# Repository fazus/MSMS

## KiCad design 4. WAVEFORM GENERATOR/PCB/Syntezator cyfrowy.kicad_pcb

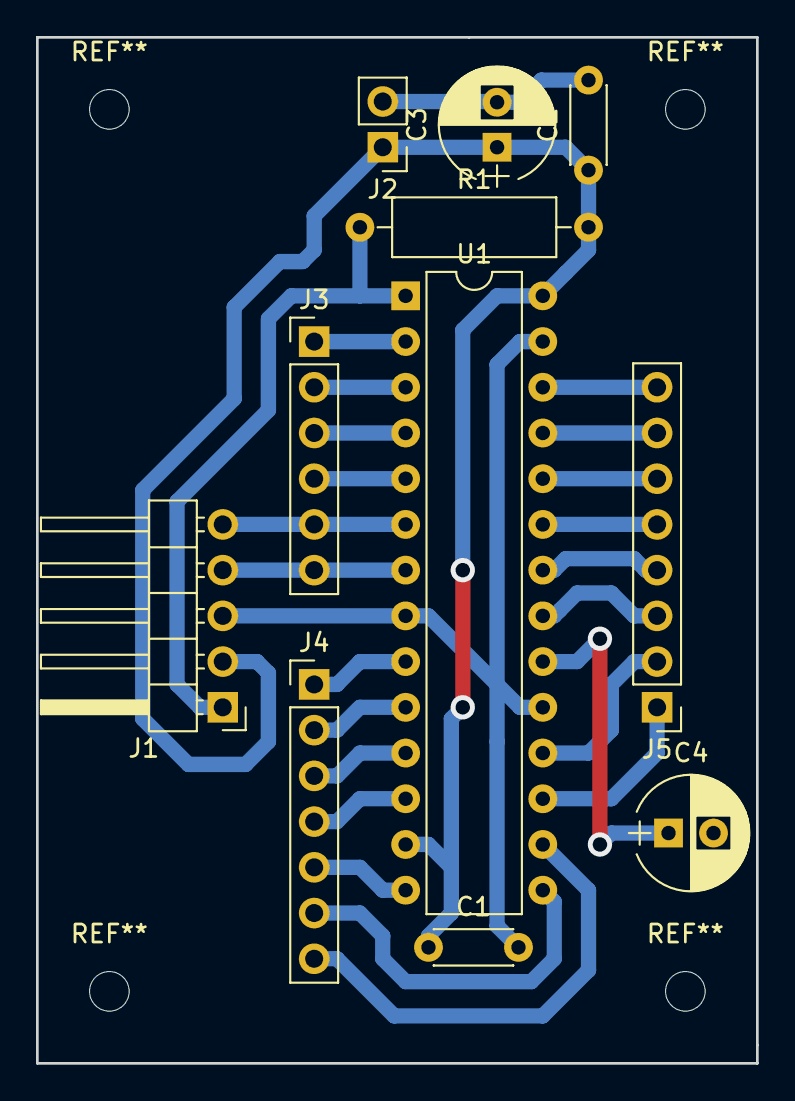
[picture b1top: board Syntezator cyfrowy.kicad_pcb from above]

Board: 2 copper layers, 40.0 x 57.0 mm, 11 parts (0 on the bottom side), 25 nets.

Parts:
C1, C2: C; C_Disc_D4.3mm_W1.9mm_P5.00mm
C3, C4: CP; CP_Radial_D6.3mm_P2.50mm
J1: Conn_01x05; Pin_Header_Angled_1x05_Pitch2.54mm
J2: Conn_01x02; Pin_Header_Straight_1x02_Pitch2.54mm
J3: Conn_01x06; Pin_Header_Straight_1x06_Pitch2.54mm
J4: Conn_01x07; Pin_Header_Straight_1x07_Pitch2.54mm
J5: Conn_01x08; Pin_Header_Straight_1x08_Pitch2.54mm
R1: R; R_Axial_DIN0309_L9.0mm_D3.2mm_P12.70mm_Horizontal
U1: DSPIC33EP256GP502; DIP-28_W7.62mm

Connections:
+3V3: C1.1, C2.1, C3.1, J1.2, J2.1, R1.2, U1.13, U1.28
GND: C1.2, C2.2, C3.2, C4.2, J1.3, J2.2, U1.8, U1.19, U1.27
unnamed: C4.1, U1.20
unnamed: J1.1, R1.1, U1.1
unnamed: J1.4, J3.6, U1.7
unnamed: J1.5, J3.5, U1.6
unnamed: J3.1, U1.2
unnamed: J3.2, U1.3
unnamed: J3.3, U1.4
unnamed: J3.4, U1.5
unnamed: J4.1, U1.9
unnamed: J4.2, U1.10
unnamed: J4.3, U1.11
unnamed: J4.4, U1.12
unnamed: J4.5, U1.14
unnamed: J4.6, U1.15
unnamed: J4.7, U1.16
unnamed: J5.1, U1.17
unnamed: J5.2, U1.18
unnamed: J5.3, U1.21
unnamed: J5.4, U1.22
unnamed: J5.5, U1.23
unnamed: J5.6, U1.24
unnamed: J5.7, U1.25
unnamed: J5.8, U1.26

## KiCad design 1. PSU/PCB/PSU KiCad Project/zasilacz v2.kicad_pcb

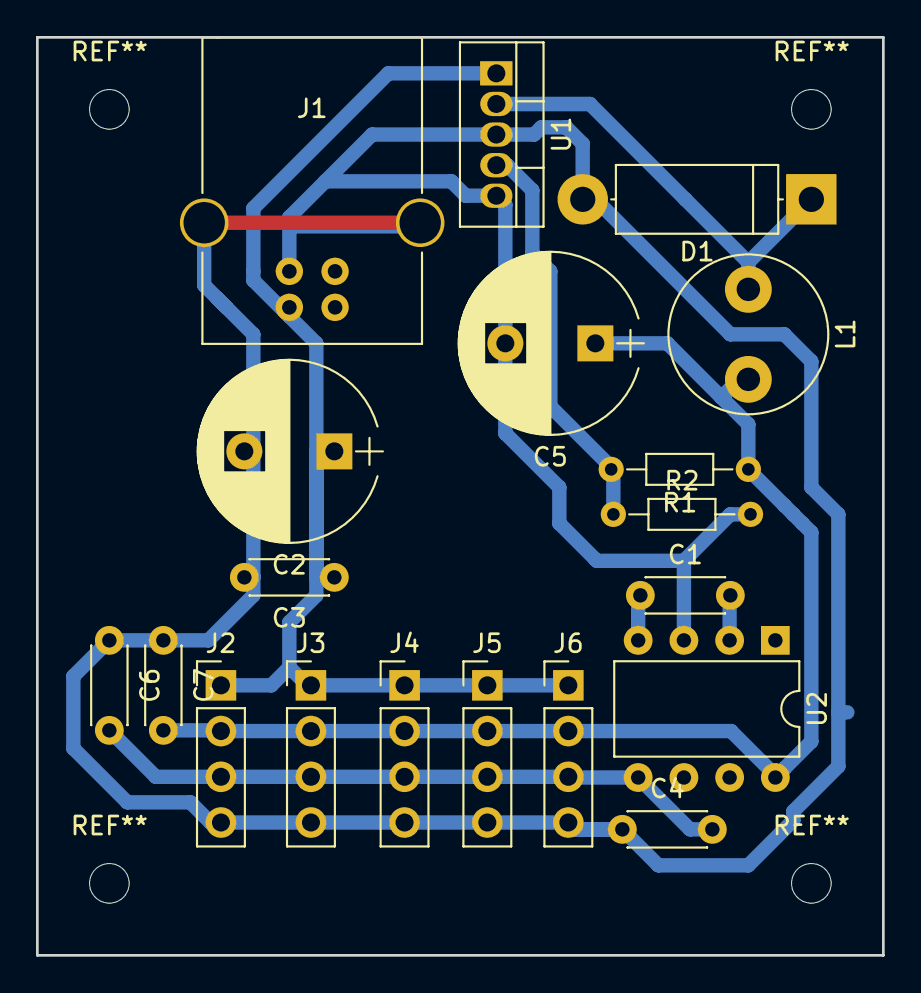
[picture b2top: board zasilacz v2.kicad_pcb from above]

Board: 2 copper layers, 47.0 x 51.0 mm, 19 parts (0 on the bottom side), 8 nets.

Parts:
C1, C3, C4, C6, C7: C; C_Disc_D4.3mm_W1.9mm_P5.00mm
C2, C5: CP; CP_Radial_D10.0mm_P5.00mm
D1: D_Schottky; D_5W_P12.70mm_Horizontal
J1: USB_B
J2, J3, J4, J5, J6: Conn_01x04; Pin_Header_Straight_1x04_Pitch2.54mm
L1: L; L_Radial_D8.7mm_P5.00mm_Fastron_07HCP
R1, R2: R; R_Axial_DIN0204_L3.6mm_D1.6mm_P7.62mm_Horizontal
U1: MIC4576; TO-220-5_Vertical
U2: TC7660H; DIP-8_W7.62mm

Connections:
+3V3: C5.1, C7.2, J2.2, J3.2, J4.2, J5.2, J6.2, L1.2, R1.1, U2.8
+5V: C2.1, C3.1, J1.1, J2.1, J3.1, J4.1, J5.1, J6.1, U1.1
-3V3: C4.2, C6.2, J2.3, J3.3, J4.3, J5.3, J6.3, U2.5
GND: C2.2, C3.2, C4.1, C5.2, C6.1, C7.1, D1.2, J1.4, J1.5, J2.4, J3.4, J4.4, J5.4, J6.4, R2.2, U1.3, U1.5, U2.3
unnamed: C1.1, U2.4
unnamed: C1.2, U2.2
unnamed: D1.1, L1.1, U1.2
unnamed: R1.2, R2.1, U1.4

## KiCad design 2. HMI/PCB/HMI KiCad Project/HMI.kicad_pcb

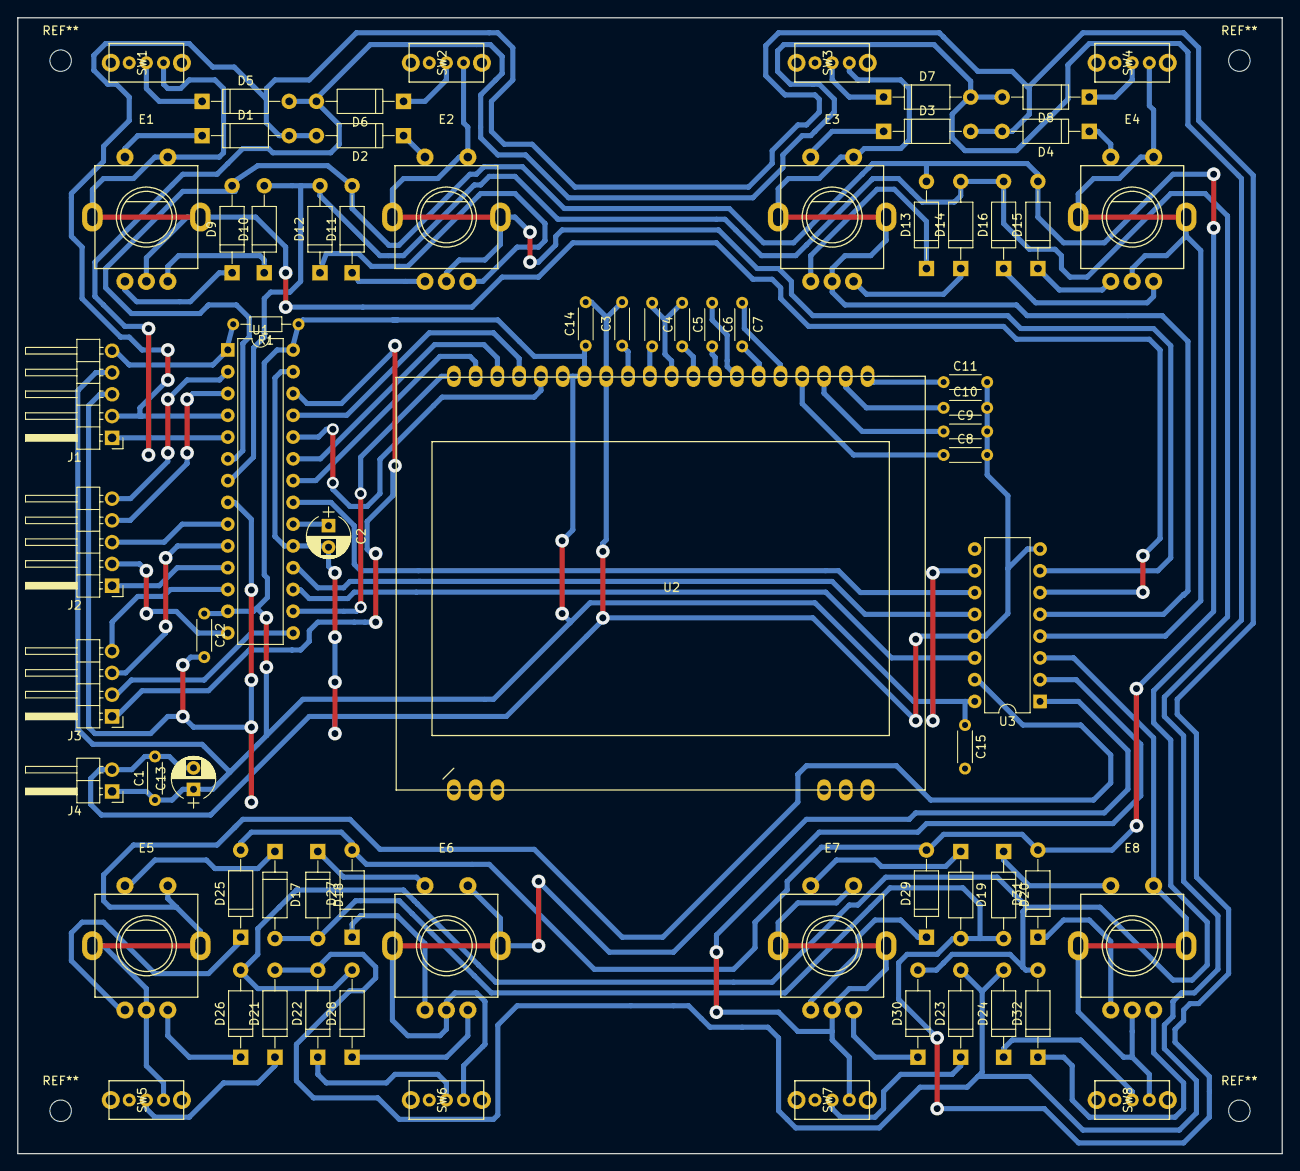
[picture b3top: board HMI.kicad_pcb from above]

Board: 2 copper layers, 147.5 x 132.5 mm, 71 parts (0 on the bottom side), 76 nets.

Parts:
C1, C3, C4, C5, C6, C7, C8, C9, C10, C11, C12, C14, C15: C; R_Axial_DIN0204_L3.6mm_D1.6mm_P5.08mm_Horizontal
C2, C13: CP; CP_Radial_D5.0mm_P2.50mm
D1, D2, D3, D4, D5, D6, D7, D8, D9, D10, D11, D12, D13, D14, D15, D16, D17, D18, D19, D20, D21, D22, D23, D24, D25, D26, D27, D28, D29, D30, D31, D32: D_Schottky; D_A-405_P10.16mm_Horizontal
E1, E2, E3, E4, E5, E6, E7, E8: Enkoder; EC11
J1, J2: Conn_01x05; Pin_Header_Angled_1x05_Pitch2.54mm
J3: Conn_01x04; Pin_Header_Angled_1x04_Pitch2.54mm
J4: Conn_01x02; Pin_Header_Angled_1x02_Pitch2.54mm
R1: R; R_Axial_DIN0204_L3.6mm_D1.6mm_P7.62mm_Horizontal
SW1, SW2, SW3, SW4, SW5, SW6, SW7, SW8: SW_DIP_x01; przelacznik_suwakowy
U1: PIC32MX130F064D-I/PT; DIP-28_W7.62mm
U2: DOGL128-E; DOGL128
U3: 74HC595; DIP-16_W7.62mm

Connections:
+3V3: C1.1, C12.1, C13.1, C14.1, C15.1, J1.4, J4.1, R1.1, U1.13, U1.28, U2.34, U2.35, U3.10, U3.16
GND: C1.2, C2.2, C3.2, C7.2, C8.2, C9.2, C10.2, C11.2, C12.2, C13.2, C14.2, C15.2, J1.3, J4.2, U1.8, U1.19, U1.27, U2.26, U2.33, U3.8, U3.13
unnamed: C2.1, U1.20
unnamed: C3.1, U2.32
unnamed: C4.1, C5.1, U2.30
unnamed: C4.2, U2.31
unnamed: C5.2, U2.29
unnamed: C6.1, U2.27
unnamed: C6.2, U2.28
unnamed: C7.1, U2.25
unnamed: C8.1, U2.24
unnamed: C9.1, U2.23
unnamed: C10.1, U2.22
unnamed: C11.1, U2.21
unnamed: D1.1, E1.4
unnamed: D1.2, D2.2, D3.2, D4.2, D17.2, D18.2, D19.2, D20.2, J1.2, U1.4
unnamed: D2.1, E2.4
unnamed: D3.1, E3.4
unnamed: D4.1, E4.4
unnamed: D5.1, SW1.2
unnamed: D6.1, SW2.2
unnamed: D7.1, SW3.2
unnamed: D8.1, SW4.2
unnamed: D9.1, E1.1
unnamed: D10.1, E1.3
unnamed: D10.2, D12.2, D14.2, D16.2, D26.2, D28.2, D30.2, D32.2, U1.7
unnamed: D11.1, E2.1
unnamed: D9.2, D11.2, D13.2, D15.2, D25.2, D27.2, D29.2, D31.2, U1.6
unnamed: D12.1, E2.3
unnamed: D13.1, E3.1
unnamed: D14.1, E3.3
unnamed: D15.1, E4.1
unnamed: D16.1, E4.3
unnamed: D17.1, E5.4
unnamed: D18.1, E6.4
unnamed: D19.1, E7.4
unnamed: D20.1, E8.4
unnamed: D21.1, SW5.2
unnamed: D5.2, D6.2, D7.2, D8.2, D21.2, D22.2, D23.2, D24.2, J1.1, U1.5
unnamed: D22.1, SW6.2
unnamed: D23.1, SW7.2
unnamed: D24.1, SW8.2
unnamed: D25.1, E5.1
unnamed: D26.1, E5.3
unnamed: D27.1, E6.1
unnamed: D28.1, E6.3
unnamed: D29.1, E7.1
unnamed: D30.1, E7.3
unnamed: D31.1, E8.1
unnamed: D32.1, E8.3
unnamed: E1.2, E1.5, E1.6, SW1.1, U3.6
unnamed: E2.2, E2.5, E2.6, SW2.1, U3.7
unnamed: E3.2, E3.5, E3.6, SW3.1, U3.5
unnamed: E4.2, E4.5, E4.6, SW4.1, U3.4
unnamed: E5.2, E5.5, E5.6, SW5.1, U3.15
unnamed: E6.2, E6.5, E6.6, SW6.1, U3.1
unnamed: E7.2, E7.5, E7.6, SW7.1, U3.2
unnamed: E8.2, E8.5, E8.6, SW8.1, U3.3
unnamed: J1.5, R1.2, U1.1
unnamed: J2.1, U1.11
unnamed: J2.2, U1.14
unnamed: J2.3, U1.9
unnamed: J2.4, U1.3
unnamed: J2.5, U1.2
unnamed: J3.1, U1.26
unnamed: J3.2, U1.15
unnamed: J3.3, U1.10
unnamed: J3.4, U1.12
unnamed: U1.16, U2.40
unnamed: U1.17, U3.14
unnamed: U1.18, U3.12
unnamed: U1.21, U3.11
unnamed: U1.22, U2.39
unnamed: U1.23, U2.38
unnamed: U1.24, U2.36
unnamed: U1.25, U2.37

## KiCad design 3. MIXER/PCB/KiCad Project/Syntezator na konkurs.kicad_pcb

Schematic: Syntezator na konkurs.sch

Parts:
C1: CP; C_Disc_D10.5mm_W5.0mm_P5.00mm
C2, C12, C13: CP; CP_Radial_D8.0mm_P3.50mm
C3, C4, C5: C; C_Disc_D5.0mm_W2.5mm_P2.50mm
C6, C7: C; C_Disc_D3.0mm_W1.6mm_P2.50mm
C8, C9, C10, C11, C14: CP; CP_Radial_D5.0mm_P2.50mm
J1: Conn_01x02; Socket_Strip_Straight_1x02_Pitch2.54mm
J2, J4: Conn_01x06; Socket_Strip_Straight_1x06_Pitch2.54mm
J3: Conn_01x05; Socket_Strip_Straight_1x05_Pitch2.54mm
J6: Audio-Jack-3_2Switches; jack35mm_wo_switch
J7: Conn_02x05_Odd_Even; Socket_Strip_Straight_2x05_Pitch2.54mm
R1, R2, R3, R4, R5, R6, R7, R8, R9, R10, R11, R12, R13, R14, R15, R16, R17, R18, R19, R20, R21, R22, R23, R24, R25: R; R_Axial_DIN0207_L6.3mm_D2.5mm_P10.16mm_Horizontal
RV1, RV2, RV3, RV4, RV5: R_POT; Potentiometer_Trimmer_VishaySpectrol_Econtrim-Type36M
U1: DSPIC33FJ128GP802; DIP-28_W7.62mm_LongPads
U2: MCP602; DIP-8_W7.62mm_Socket
U3: MCP604; DIP-14_W7.62mm_grube_pady
U4: MCP602; DIP-8_W7.62mm

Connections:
+3V3: C2.1, C3.1, C4.1, C5.1, C6.1, C7.1, J1.2, J3.2, R1.1, R2.2, R10.1, U1.13, U1.28, U2.8 (V+), U3.4 (V+), U4.8 (V+)
GND: C1.2, C2.2, C3.2, C4.2, C5.2, C6.2, C7.2, J1.1, J3.3, J6.3, J7.2, J7.4, J7.6, J7.8, J7.10, R3.1, R12.2, RV1.3, RV2.3, RV3.3, RV4.3, RV5.3, U1.8, U1.19, U1.27, U2.4 (V-), U3.11 (V-), U4.4 (V-)
unnamed: C1.1, U1.20
unnamed: C8.1, R5.2
unnamed: C8.2, RV1.2
unnamed: C9.1, R7.2
unnamed: C9.2, RV2.2
unnamed: C10.1, R9.2
unnamed: C10.2, RV3.2
unnamed: C11.1, R19.2
unnamed: C11.2, RV4.2
unnamed: C12.1, R23.1
unnamed: C12.2, J6.2
unnamed: C13.1, R24.1
unnamed: C13.2, J6.1
unnamed: C14.1, R25.2
unnamed: C14.2, RV5.2
unnamed: J2.1, U1.15
unnamed: J2.2, U1.16
unnamed: J2.3, U1.17
unnamed: J2.4, U1.18
unnamed: J2.5, U1.21
unnamed: J2.6, U1.22
unnamed: J3.1, R1.2, U1.1
unnamed: J3.4, R14.1, U1.4, U3.14
unnamed: J3.5, R8.1, U1.5, U3.8
unnamed: J4.1, U1.7
unnamed: J4.2, U1.9
unnamed: J4.3, U1.10
unnamed: J4.4, U1.11
unnamed: J4.5, U1.12
unnamed: J4.6, U1.14
unnamed: J7.1, RV1.1
unnamed: J7.3, RV2.1
unnamed: J7.5, RV3.1
unnamed: J7.7, RV4.1
unnamed: J7.9, RV5.1
unnamed: R2.1, R3.2, U4.3 (+)
unnamed: R4.1, U1.3, U3.1
unnamed: R4.2, R5.1, U3.2 (-)
unnamed: R6.1, U1.2, U3.7
unnamed: R6.2, R7.1, U3.6 (-)
unnamed: R8.2, R9.1, U3.9 (-)
unnamed: R10.2, R11.1, R12.1, R13.2
unnamed: R11.2, R17.2, U1.23
unnamed: R13.1, R15.2, U1.25
unnamed: R14.2, R19.1, U3.13 (-)
unnamed: R15.1, U2.5 (+)
unnamed: R16.1, R20.2, U2.6 (-)
unnamed: R16.2, U1.26
unnamed: R17.1, U2.3 (+)
unnamed: R18.1, R21.2, U2.2 (-)
unnamed: R18.2, U1.24
unnamed: R20.1, R24.2, U2.7
unnamed: R21.1, R23.2, U2.1
unnamed: R22.1, U1.6, U4.7
unnamed: R22.2, R25.1, U4.6 (-)
unnamed: U3.3 (+), U3.5 (+), U3.10 (+), U3.12 (+), U4.1, U4.2 (-), U4.5 (+)

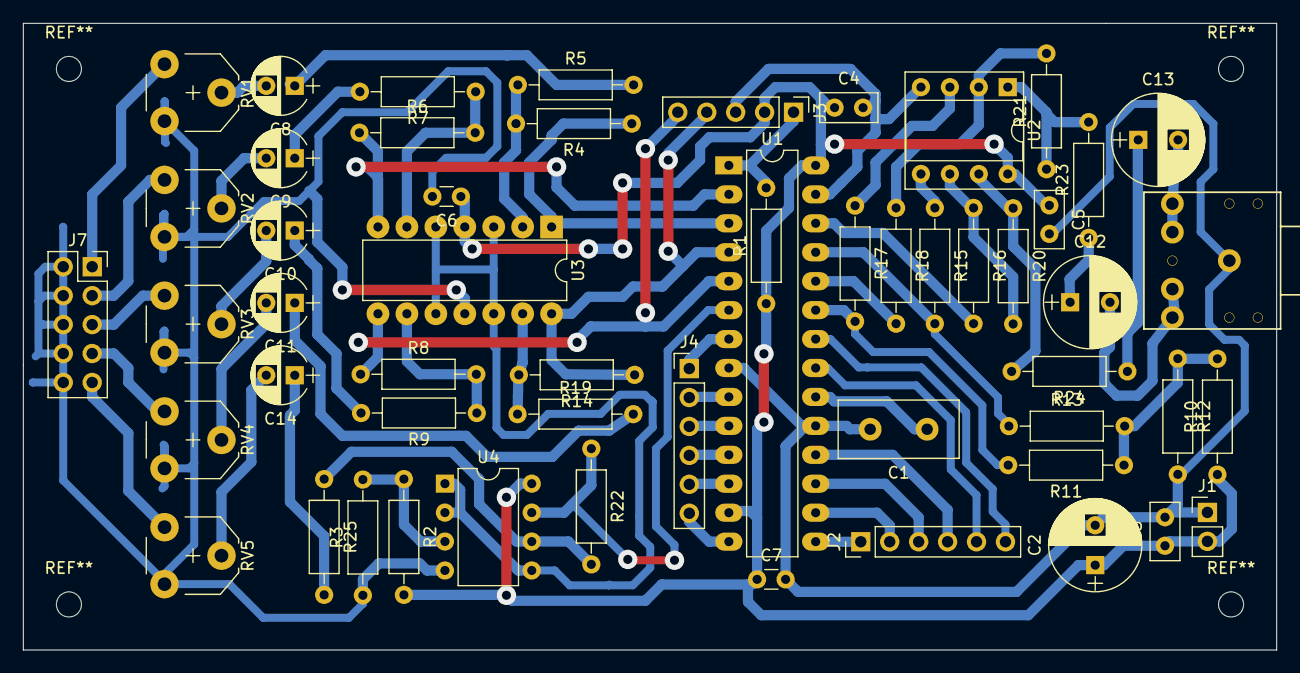
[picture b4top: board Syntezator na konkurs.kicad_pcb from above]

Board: 2 copper layers, 110.0 x 55.0 mm, 54 parts (0 on the bottom side), 58 nets.

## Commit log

2018-08-27 PSU KiCad Project
2018-08-27 PSU layout
2018-08-27 PSU pdf
2018-09-02 nowe rzeczy
2018-09-02 pprawk
2018-09-04 Human to Machine Interface board
2018-09-04 Amiga rulez
2018-09-07 DUPER
2018-09-09 Ulepszenia
2018-09-10 Dobro wraca
2018-09-10 nowe
2018-09-16 nowe super rzeczy
2018-09-24 cos przestawić bądź cos wstawić
2018-10-15 Create LICENSE
